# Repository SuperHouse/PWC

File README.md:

Permobil Wheelchair Controller
==============================
Copyright 2021 SuperHouse Automation Pty Ltd <www.superhouse.tv>  
Designed by Jonathan Oxer and Chris Fryer.

Connects to a Permobil electric wheelchair controller, and emulates the
signals from a wheelchair joystick so that the chair can be controlled
electronically.

Includes an I2C header so that a ZeroStick zero deflection joystick can
be connected.

Includes an ESP32 so that the chair can be controlled using WiFi or
Bluetooth. The example firmware includes support for both PS3 and PS4
game controllers.

Also exposes the "5th Button" input to the chair as a test point for
experimentation.

Features:

 * 1 x chair controller output.
 * Derives 12V from the host wheelchair controller for reference
    voltage.
 * Requires 5V power via USB.

More information is available at:

  http://www.superhouse.tv/pwc

INSTALLATION
------------
The design is saved as an EAGLE project. To use this project download
it and place the directory containing these files into the "eagle"
directory on your computer. Then open EAGLE and navigate to the project.

DISTRIBUTION
------------
The specific terms of distribution of this project are governed by the
license referenced below.

LICENSE
-------
Licensed under the TAPR Open Hardware License (www.tapr.org/OHL).
The "license" folder within this repository also contains a copy of
this license in plain text format.

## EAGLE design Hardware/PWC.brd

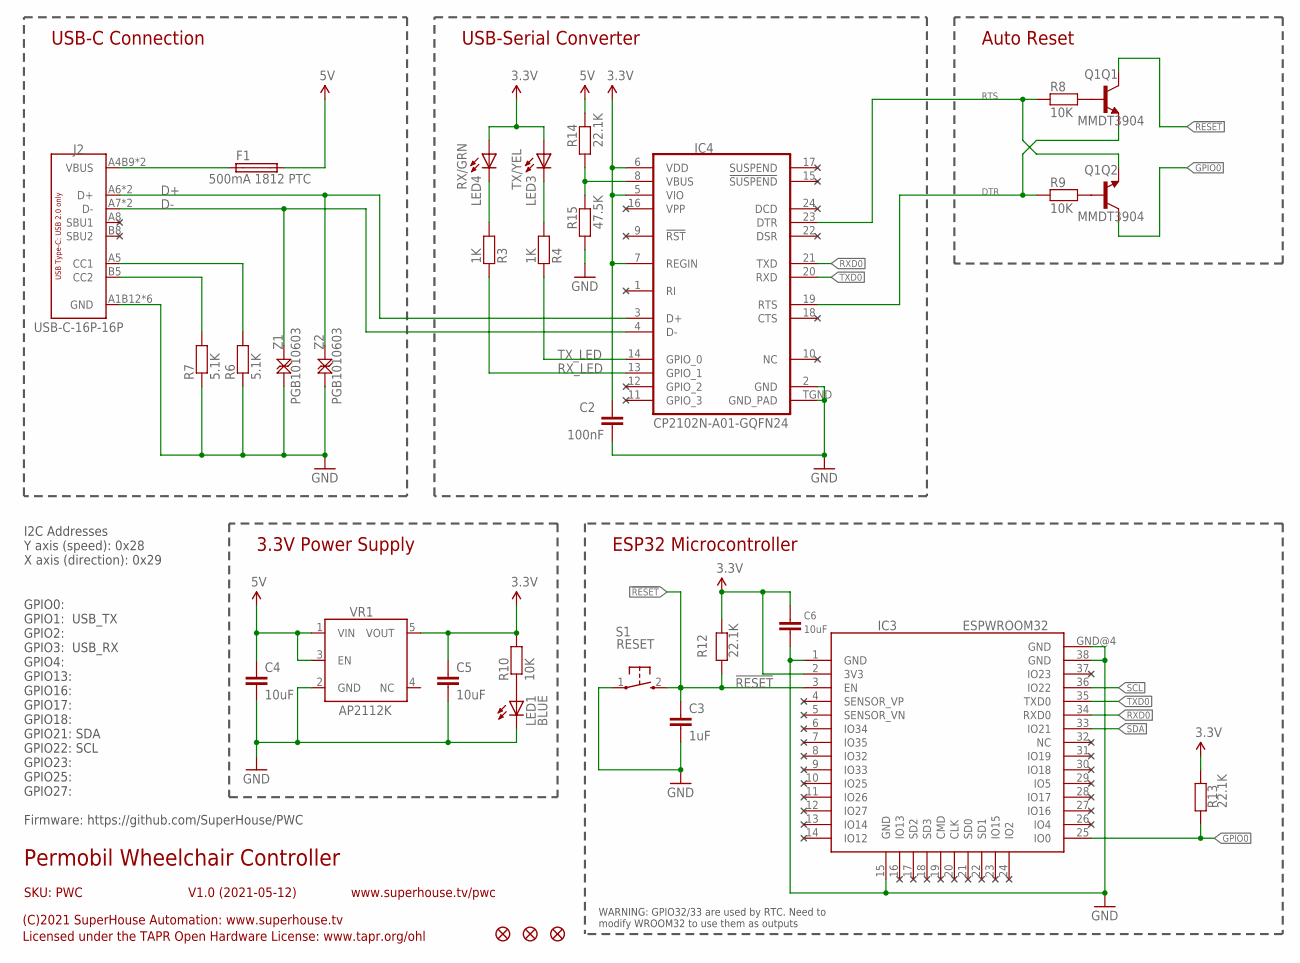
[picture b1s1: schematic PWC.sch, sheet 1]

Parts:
C2: 100nF; C0603
C3: 1uF; C0603
C4, C5, C6: 10uF; C0805
F1: 500mA 1812 PTC; 1812
IC3: ESPWROOM32
IC4: CP2102N-A01-GQFN24; QFN-24
J2: USB-C-16P-16P; USB-C-16P
LED1: BLUE; LED-0603
LED3: TX/YEL; LED-0603
LED4: RX/GRN; LED-0603
Q1: MMDT3904; SOT-363
R3, R4: 1K; R0603
R6, R7: 5.1K; R0603
R8, R9, R10: 10K; R0603
R12, R13, R14: 22.1K; R0603
R15: 47.5K; R0603
S1: RESET; TACTILE_SMT_3X4X2
U$35, U$36, U$37: FIDUCIAL1X2; FIDUCIAL-1X2
VR1: AP2112KSOT25; SOT23-5
Z1, Z2: PGB1010603; TVS0603

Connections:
3.3V: C2.1, C5.1, C6.1, IC3.2 (3V3), IC4.5 (VIO), IC4.6 (VDD), IC4.7 (REGIN), LED3.A, LED4.A, R10.2, R12.1, R13.1, VR1.5 (VOUT); also elsewhere on the board
5V: C4.1, F1.2, R14.2, VR1.1 (VIN), VR1.3 (EN)
!RESET: C3.1, IC3.3 (EN), Q1.3 (C), R12.2, S1.2 (S)
D+: IC4.3 (D+), J2.A6 (D+), J2.B6 (D+), Z2.2
D-: IC4.4 (D-), J2.A7 (D-), J2.B7 (D-), Z1.2
DTR: IC4.23 (DTR), Q1.1 (E), R8.1
GND: C2.2, C3.2, C4.2, C5.2, C6.2, IC3.1 (GND), IC3.15 (GND), IC3.38 (GND), IC3.GND@4 (GND), IC4.2 (GND), IC4.TGND (GND_PAD), J2.A1B12 (GND), J2.A12B1 (GND), J2.FIX1 (GND), J2.FIX2 (GND), J2.FIX3 (GND), J2.FIX4 (GND), LED1.C, R6.1, R7.1, R15.1, S1.1, VR1.2 (GND), Z1.1, Z2.1; also elsewhere on the board
GPIO0: IC3.25 (IO0), Q1.6 (C), R13.2
unnamed: LED1.A, R10.1
unnamed: Q1.5 (B), R8.2
unnamed: Q1.2 (B), R9.2
unnamed: LED4.C, R3.2
unnamed: J2.B5 (CC2), R7.2
unnamed: J2.A5 (CC1), R6.2
unnamed: LED3.C, R4.2
unnamed: IC4.8 (VBUS), R14.1, R15.2
RTS: IC4.19 (RTS), Q1.4 (E), R9.1
RXD0: IC3.34 (RXD0), IC4.21 (TXD)
RX_LED: IC4.13 (GPIO_1), R3.1
SCL: IC3.36 (IO22); also elsewhere on the board
SDA: IC3.33 (IO21); also elsewhere on the board
TXD0: IC3.35 (TXD0), IC4.20 (RXD)
TX_LED: IC4.14 (GPIO_0), R4.1
VIN: F1.1, J2.A4B9 (VBUS), J2.A9B4 (VBUS)

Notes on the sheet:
USB-C Connection
USB-Serial Converter
Auto Reset
3.3V Power Supply
ESP32 Microcontroller
WARNING: GPIO32/33 are used by RTC. Need to modify WROOM32 to use them as outputs
GPIO0: GPIO1: USB_TX GPIO2: GPIO3: USB_RX GPIO4: GPIO13: GPIO16: GPIO17: GPIO18: GPIO21: SDA GPIO22: SCL GPIO23: GPIO25: GPIO27: Firmware: https://github.com/SuperHouse/PWC
Permobil Wheelchair Controller
V1.0 (2021-05-12)
SKU: PWC
(C)2021 SuperHouse Automation: www.superhouse.tv
Licensed under the TAPR Open Hardware License: www.tapr.org/ohl
www.superhouse.tv/pwc
I2C Addresses Y axis (speed): 0x28 X axis (direction): 0x29

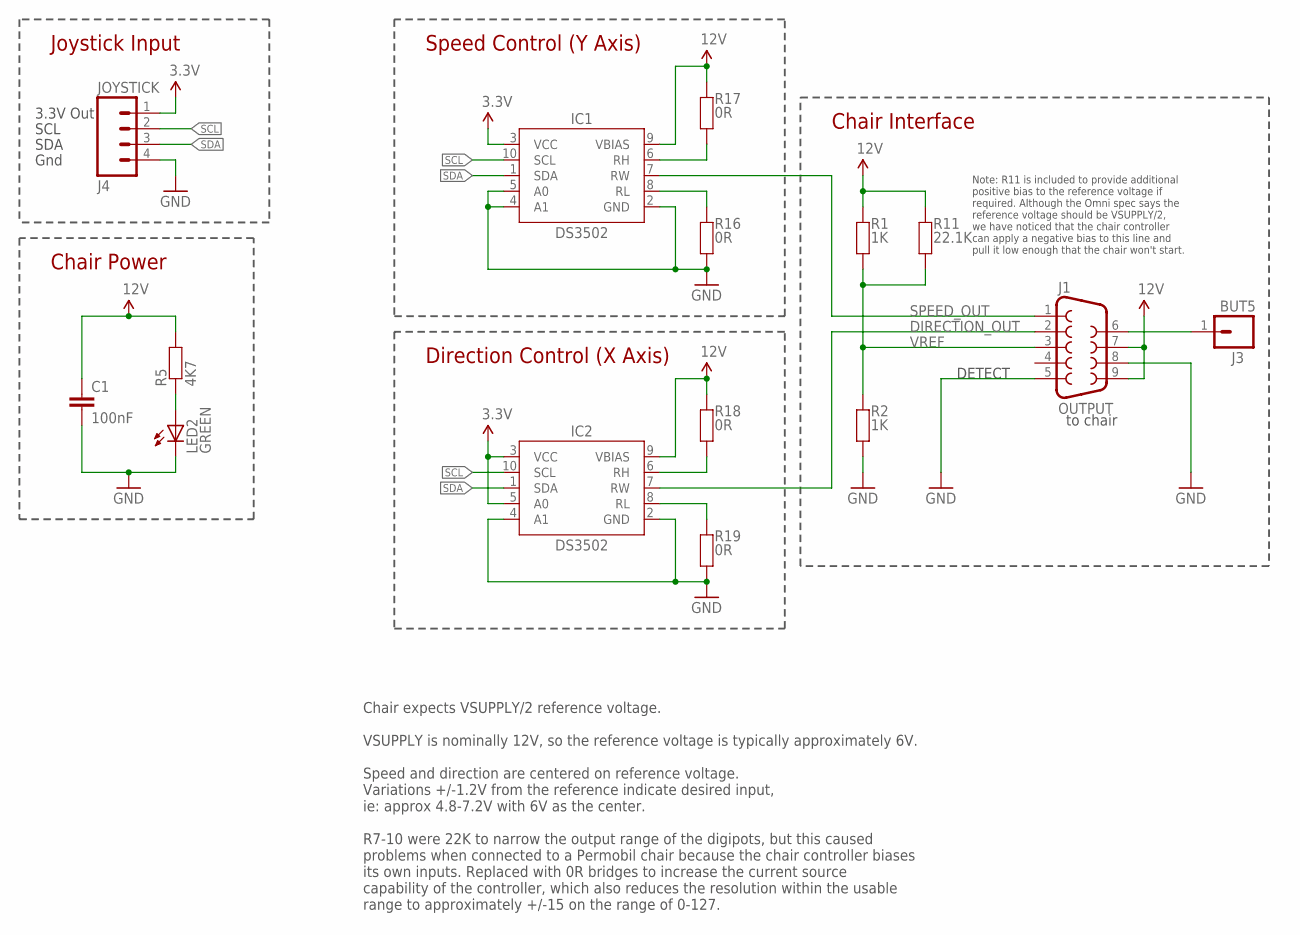
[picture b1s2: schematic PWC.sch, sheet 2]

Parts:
C1: 100nF; C0603
IC1, IC2: DS3502; MSOP10
J1: OUTPUT; DB9-PCB-SOCKET
J3: BUT5; 1X01
J4: JOYSTICK; 1X04
LED2: GREEN; LED-0603
R1, R2: 1K; R0603
R5: 4K7; R0603
R11: 22.1K; R0603
R16, R17, R18, R19: 0R; R0603

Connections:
3.3V: IC1.3 (VCC), IC2.3 (VCC), IC2.5 (A0), J4.1; also elsewhere on the board
12V: C1.1, IC1.9 (VBIAS), IC2.9 (VBIAS), J1.7, J1.9, R1.2, R5.2, R11.2, R17.2, R18.2
BUT5: J1.6, J3.1
DIRECTION_OUT: IC2.7 (RW), J1.2
GND: C1.2, IC1.2 (GND), IC1.4 (A1), IC1.5 (A0), IC2.2 (GND), IC2.4 (A1), J1.5, J1.8, J4.4, LED2.C, R2.1, R16.1, R19.1; also elsewhere on the board
unnamed: IC1.6 (RH), R17.1
unnamed: IC2.6 (RH), R18.1
unnamed: IC1.8 (RL), R16.2
unnamed: LED2.A, R5.1
unnamed: IC2.8 (RL), R19.2
SCL: IC1.10 (SCL), IC2.10 (SCL), J4.2; also elsewhere on the board
SDA: IC1.1 (SDA), IC2.1 (SDA), J4.3; also elsewhere on the board
SPEED_OUT: IC1.7 (RW), J1.1
VREF: J1.3, R1.1, R2.2, R11.1

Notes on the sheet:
to chair
Direction Control (X Axis)
Speed Control (Y Axis)
Chair Interface
Note: R11 is included to provide additional positive bias to the reference voltage if required. Although the Omni spec says the reference voltage should be VSUPPLY/2, we have noticed that the chair controller can apply a negative bias to this line and pull it low enough that the chair won't start.
DETECT
Chair Power
Chair expects VSUPPLY/2 reference voltage. VSUPPLY is nominally 12V, so the reference voltage is typically approximately 6V. Speed and direction are centered on reference voltage. Variations +/-1.2V from the reference indicate desired input, ie: approx 4.8-7.2V with 6V as the center. R7-10 were 22K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
Joystick Input
3.3V Out
SCL
SDA
Gnd

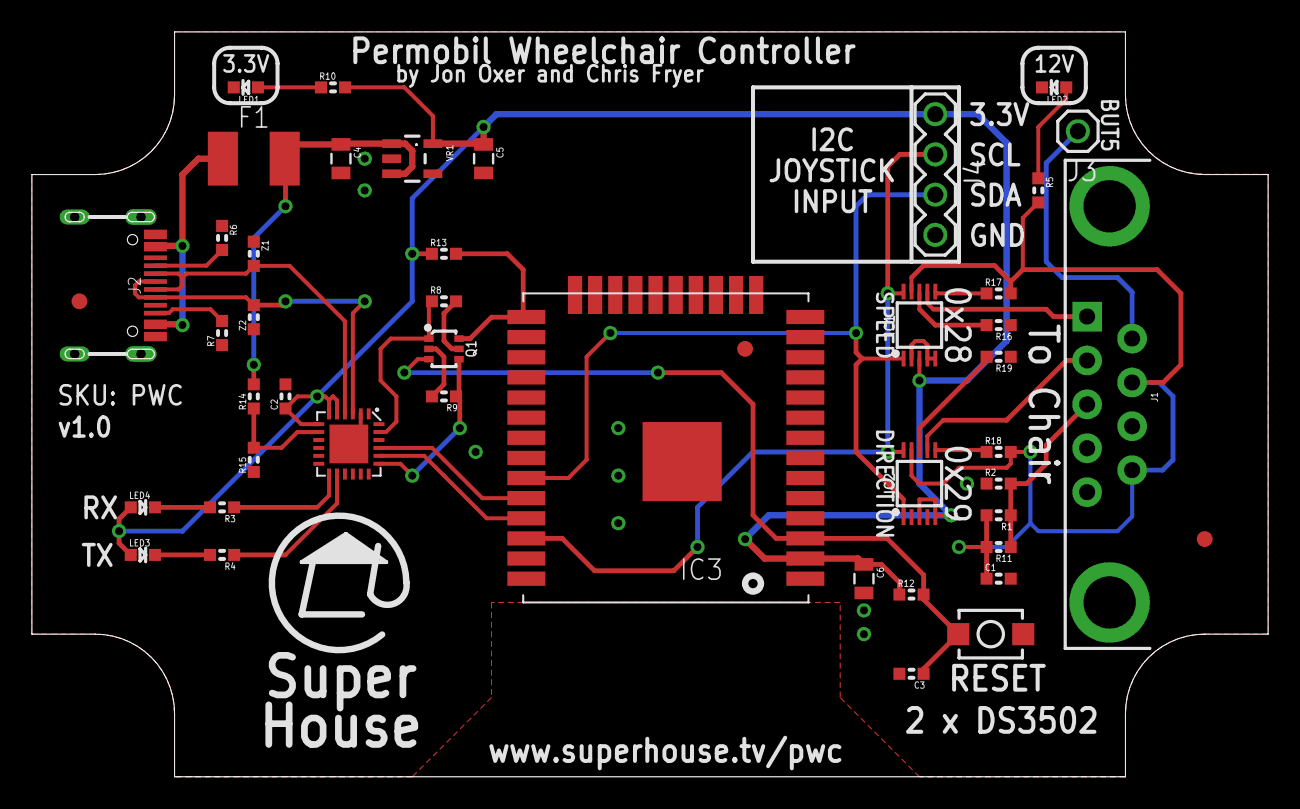
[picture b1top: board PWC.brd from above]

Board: 2 copper layers, 78.0 x 47.0 mm, 46 parts (0 on the bottom side), 34 nets.

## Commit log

2021-05-25 Added .gitignore.
2021-05-25 Initial project import.
2021-05-25 Adjusted README to suit PWC project.
2021-05-25 Copied in ZeroStick firmware as a starting point.
2021-05-25 Copied the correct firmware this time!
2021-05-25 Removed irrelevant parts of ZeroStick firmware and changes for ESP32.
2021-05-25 Added photo of prototype.
2021-06-23 Preliminary support for PS4 (BLE) game controller as input. Made input type selectable in config. Made debugging more configurable in config.
2021-06-30 Added support for PS3 controller as input.
2021-06-30 If a PS3 controller has been paired, disable the ZeroStick input.
2021-06-30 Remove startup delay to prevent Permobil controller out-of-center error.
2021-07-06 Fixed PS4 controller connection. Reversed Y axis on PS4 controller. Report battery level and charge state for PS4 controller.
2021-07-06 Clarified game controller input value ranges. Made example BLE MAC address more generic. Bumped software version to v2.2.
2021-07-06 Updated parts to use the new SuperHouse Eagle libraries.
